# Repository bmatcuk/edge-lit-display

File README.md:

# Edge-lit Display
This repository contains everything you need to build an edge-lit display using
RGB LEDs and laser etched acrylic with a laser cut enclosure.

## System Overview
The display is controlled by an [ATmega32U4], the same microcontroller used in
several [Arduino] boards. It is flashed as an [Arduino Leonardo] over the ICSP
header to make it easier to work with, using an actual [Arduino] as the
programmer. The design surrounding the [ATmega32U4] support circuitry, including
the USB connections, is based on the [Arduino Leonardo] schematics.

The microcontroller communicates with a [TLC5971] over SPI to drive the eight
RGB LEDs. The [TLC5971] is a 12-channel, constant-current sink, 16-bit PWM LED
driver (ie, capable of driving four RGB LEDs at a time). Therefore, the eight
RGB LEDs are divided into two groups and time-multiplexed by the
microcontroller using two high-side PMOS transistors. This allows us to address
each channel of each LED individually.

This circuit is then fitted into a laser cut enclosure with the LEDs directed
into the edge of a laser etched acrylic display. The code on the
microcontroller cycles the colors of the LEDs by rotating through all possible
values for "hue" in the HCY (hue-chroma-luma) colorspace, and converting to 16-
bit RGB for transmission to the [TLC5971].

The whole thing is powered using a standard USB 2.0 cable and includes a
potentiometer to control the brightness of the LEDs by varying the current-
setting resistance of the [TLC5971].

## Schematics
Schematics were designed in [KiCad] v4. This repository has a dependency on my
own [part library] and assumes that my [part library] is located in the same
path as this repository (ie, the `edge-lit display` and `bmatcuk-kicad-library`
directories live in the same directory).

This first schematic is the [ATmega32U4], USB, and support circuitry:

The next schematic connects the microcontroller to the LEDs, driver, and high-
side PMOS to time-multiplex the LED groups:

## PCB Layout
The PCB was designed in [KiCad] v4. This repository has a dependency on my
own [part library] and assumes that my [part library] is located in the same
path as this repository (ie, the `edge-lit display` and `bmatcuk-kicad-library`
directories live in the same directory).

The circuit is laid out as a two-layer design. The front layer contains all of
the components and a ground plane with the back layer as a signal layer. This
is probably the weakest part of the whole project as this is the first time
I've laid out a circuit with so many surface mount components in a constrained
space.

## Enclosure
The enclosure was designed in [FreeCAD] 0.17 assuming it would be made out of
MDF wood with a thickness of 0.251in and laser kerf of 0.011in. The screen
was designed for acrylic with a thickness of 3mm and a laser kerf of 0.2mm.
These values can be easily modified in [FreeCAD] by editing the spreadsheet
called "Datum"; the rest of the design will update automatically.

Once the design was complete, 2D projections were made of each piece and these
projections were exported as "flattened svgs". The resulting svg was edited in
[Inkscape] to conform to the format that the manufacturer wanted (ie, to make
the cuts blue, for example).

The svg below might be really difficult to see on your screen because the
stroke width is only 0.01mm. This was a requirement from where I had the
parts laser cut.

## Acrylic Screen
The outline of the screen was designed in [FreeCAD] with the enclosure. Once
the 2D projection was exported as an svg (as mentioned above), it was imported
into [Inkscape] to create the design. Originally, I was going to do some sort
of cityscape, but then I thought it would be more fun to tie this back to a
previous passion project of mine: [lasercat.party] (github: [lasercatparty])!

I edited the photo of the cat in [Photoshop] to remove the background, convert
to greyscale, and then darken some of the light areas with the burn tool, and
lighten some of the dark areas with the dodge tool. The image was then imported
into [Inkscape] and I used the "Trace Bitmap" function to vectorize it. This
was an iterative process: adjusting light and dark areas in [Photoshop], re-
importing in [Inkscape] to vectorize, etc, until I was happy with the result.
The rest of the design was done entirely in [Inkscape]. Then everything was
grouped together and flipped horizontally so that it could be etched on the
back of the acrylic.

The [Photoshop] file is also included in this repository (cat.psd).

Like above, it may be difficult to make out the edge cuts on your screen
because the stroke width is 0.01mm.

## Manufacturing
The first step was getting the PCB, enclosure, and screen manufactured. I sent
the gerbers to [ALLPCB.com] for PCB manufacturing. I'm very impressed with them
and would definitely recommend. I had the boards in my hands in less than a week
and their prices are very reasonable! The enclosure and screen svgs were sent to
[Ponoko] for laser cutting and etching. Therefore, the MDF and acrylic
thicknesses and kerfs match their specs, and the files are formatted to their
liking (blue for cuts, black for area engraving, red for line engraving; stroke
width of 0.01mm). All electrical components were ordered from [DigiKey]. This
repository includes a Bill Of Material file called `edge-lit display.csv` which
includes all of the [DigiKey] part numbers. You can upload the file to their
website to add all of the parts to your cart.

## Build Log
### Soldering
With PCB and components in hand, the next step is soldering the PCB. We want to
load the [Arduino] bootloader onto our [ATmega32U4], so the first thing we'll
solder is the microcontroller and support circuitry. Installing the [Arduino]
bootloader is done via the ICSP header which uses the SPI pins on the
microcontroller; these pins are also used to control the [TLC5971], so we're
going to leave that and most of the circuitry around it off our board for now.

*Technically*, I think it would be ok to solder everything before installing
the bootloader because it's unlikely that any of the data will make sense to
the [TLC5971] and the microcontroller will tri-state all of the IO pins while
flashing so all of the LEDs will be off anyway, but why risk it? Besides,
pausing to flash the microcontroller mid-solder gives us an opportunity to
make sure everything is working up to that point; troubleshooting will be
easier with fewer components on the board.

That said, I soldered all of the passives (resistors, capacitors, and the
ferrite beads), the varistors, fuse, ICSP header, diode, and [ATmega32U4]. I
technically didn't need to solder all of the passive components, since some of
them are support circuitry for the [TLC5971], but it was easier to solder them
all together. I then tested for any bridged pins with a multimeter, and, when I
was satisfied everything looked good, I moved on to installing the bootloader.

Some tips for soldering: I did most of the soldering with a soldering iron
(my trusty [Hakko FX-888D]) with a beveled tip (the [T18-CF15]). It's possible
to solder everything this way with the liberal application of flux (I have a
[Kester 186 Flux Pen]) - search for "drag soldering" tutorials. I found it
was easier to solder first using this method, and then touch things up a bit
with a hot air rework station (I'm using an [Aoyue Int866]). For example, I
soldered the [ATmega32U4] a little off-center; very hard to fix with an iron,
but short work for the hot air station.

### The Bootloader
To install the bootloader, I flashed an [Arduino Uno] with the ArduinoISP. To
do this in the [Arduino] IDE, select the Uno as the device and open the
ArduinoISP example sketch. Make sure all of the `#define`s are right at the
top of the file and then upload the sketch to the Uno. Next, disconnect the
Uno from your computer and make the following connections:
* 5V on the Uno to pin 2 of the ICSP
* GND on the Uno to pin 6 on the ICSP
* D10 on the Uno (reset signal) to pin 5 on the ICSP
* D11 on the Uno (MOSI) to pin 4 on the ICSP
* D12 on the Uno (MISO) to pin 1 on the ICSP
* D13 on the Uno (SCK) to pin 3 on the ICSP

Other [Arduino]s can be used in place of the [Arduino Uno] using a similar
process. You just need to figure out what pins are used for SPI (MOSI, MISO,
and SCK) and the reset pin. You can actually change the pins in the `#define`s
at the top of the ArduinoISP sketch.

Anyway, once the wired connections are made, reconnect the [Arduino Uno] to
your computer. Select the [Arduino Leonardo] from the device menu, set the port
to where the Uno is connected, change "programmer" to "Arduino as ISP", and
select "Burn Bootloader". This process will take a couple minutes, but it will
test to make sure installation was successful, so if you don't see any errors,
you know your soldering, at least up to this point, is good.

### Soldering Part Deux
After the bootloader is installed, disconnect the [Arduino Uno] and solder
the rest of the components. Now the sketch can be flashed via USB! Connect the
PCB to your computer via USB. If all your soldering went well, you should be
able to flash the code to it by selecting the [Arduino Leonardo] device from the
[Arduino] IDE and uploading. You should hopefully see the LEDs cycle through
all of the colors of the rainbow!

### Constructing the Enclosure
Putting the case together is fairly straightforward, but you may find that the
slots are fairly tight. The company I ordered my lasercut parts from ([Ponoko])
didn't have very accurate measurements for wood thickness or kerf. I found the
wood they sent me was around 1.5mm thicker then I was expecting. I had to use a
wood file to make the pieces fit together, and, even then, they were so snug I
didn't bother using any glue.

Basically, you want to put the bottom and sides together, gluing if necessary.
I put the lasercut side (with the burn marks) on the inside to hide it. Then
fit the PCB in. I had planned on using some M2 nylon stand-offs to mount the
PCB (hence the little holes in the top and bottom pieces), but the holes ended
up being too small to thread the stand-offs through. So, instead, I just
hammered some nails through the bottom to keep the PCB from sliding around.

Next, slide the acrylic display through the top piece and put the top of the
enclosure on. The slots on the side pieces should keep the acrylic from falling
over, and should line it up to be right on top of the LEDs. If you are
sucessfully using stand-offs, you can have some stand-offs go to the top of the
enclosure, too.

I adjusted some of the calculations in the [FreeCAD] model after I received my
lasercut enclosure to hopefully make it less snug. I also regenerated the
enclosure.svg file, but I haven't tried getting another enclosure made up.

## License
Software in this repository is licensed under the [MIT] license. Hardware
schematics are released under a Creative Commons Attribution and Share Alike
license ([CC-BY-SA] 4.0). PCB layout designs, enclosure designs, and acrylic
display designs are licensed under a Creative Commons Attribution, Non-
Commercial, Share Alike license ([CC-BY-NC-SA] 4.0).

[ALLPCB.com]: http://www.allpcb.com/
[ATmega32U4]: http://www.microchip.com/wwwproducts/en/ATmega32u4
[Aoyue Int866]: https://www.aoyue.eu/aoyue-int866-3in1-rework-station-lead-free-hot-air-soldering-station.html
[Arduino Leonardo]: https://store.arduino.cc/usa/arduino-leonardo-with-headers
[Arduino Uno]: https://store.arduino.cc/usa/arduino-uno-rev3
[Arduino]: https://www.arduino.cc/
[CC-BY-NC-SA]: https://creativecommons.org/licenses/by-nc-sa/4.0/
[CC-BY-SA]: https://creativecommons.org/licenses/by-sa/4.0/
[DigiKey]: https://www.digikey.com/
[FreeCAD]: https://www.freecadweb.org/
[Hakko FX-888D]: https://www.hakkousa.com/products/soldering/hakko-fx-888d-digital-soldering-station-10145.html
[Inkscape]: https://inkscape.org/
[Kester 186 Flux Pen]: https://www.kester.com/products/product/186-flux-pen
[KiCad]: http://kicad-pcb.org/
[MIT]: https://choosealicense.com/licenses/mit/
[Photoshop]: https://www.adobe.com/products/photoshop.html
[Ponoko]: https://www.ponoko.com/
[T18-CF15]: https://www.hakkousa.com/products/soldering-iron-tips/t18-series/t18-cf15.html
[TLC5971]: http://www.ti.com/product/TLC5971
[lasercat.party]: http://lasercat.party
[lasercatparty]: https://github.com/bmatcuk/lasercatparty
[part library]: https://github.com/bmatcuk/bmatcuk-kicad-library/

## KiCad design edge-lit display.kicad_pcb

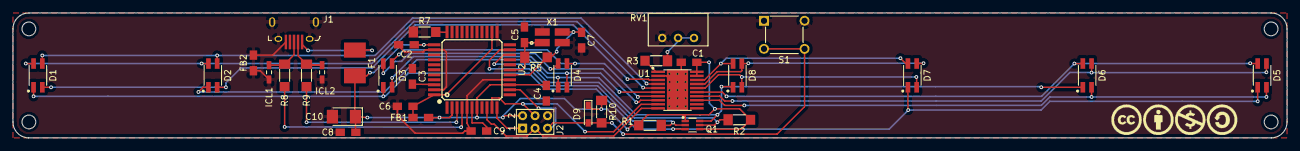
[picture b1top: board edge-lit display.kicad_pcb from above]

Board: 2 copper layers, 204.0 x 20.0 mm, 40 parts (0 on the bottom side), 35 nets.

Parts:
C1, C2, C3, C4, C8: 100nF; 0805
C5, C7: 12pF; 0805
C6, C9: 1uF; 0805
C10: 10uF; 1210
D1, D2, D3, D4, D5, D6, D7, D8: LED_ARGB; PLCC4
D9: 1N4148WS; SOD-323FL
F1: Fuse-500mA; 1812_Concave
FB1, FB2: Ferrite_Bead_30Ohm; 0805
ICL1, ICL2: Varistor; 0603
J1: USB-Micro-B; USB_Micro_B_Female
J2: CONN_03X2FEMALE; 2X3
Q1: Dual-PMOS; SOT-363
R1, R2, R7, R10: 10k; 1206
R3: 3.3k; 1206
R5: 1M; 1206
R8, R9: 22; 1206
RV1: 10k; Bourns_3310C
S1: SPST-NO; SPST_6mm
U1: TLC59711PWPR; HTSSOP-20
U2: ATMEGA32U4TQFP-44; TQFP44
X1: 16MHZ; 4SMD

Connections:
+5V: C1.1, C2.1, C4.1, C8.1, C10.1, D9.1, F1.1, FB1.1, J2.2, Q1.1, Q1.4, R1.1, R2.1, R10.2, U1.19, U1.20, U2.2, U2.7, U2.14, U2.34
/Arduino Compatible/AREF: C3.1, U2.42
/Arduino Compatible/AVCC: C6.1, FB1.2, U2.24, U2.44
/Arduino Compatible/D0: Q1.5, R2.2, U2.20
/Arduino Compatible/D1: Q1.2, R1.2, U2.21
/Arduino Compatible/D14/MISO: J2.1, U2.11
/Arduino Compatible/D15/SCK: J2.3, U1.10, U2.9
/Arduino Compatible/D16/MOSI: J2.4, U1.9, U2.10
/Arduino Compatible/D+: R8.1, U2.4
/Arduino Compatible/D-: R9.1, U2.3
/Arduino Compatible/RESET: D9.2, J2.5, R10.1, S1.3, S1.4, U2.13
/Arduino Compatible/XTAL1: C5.1, R5.2, U2.17, X1.1
/Arduino Compatible/XTAL2: C7.1, R5.1, U2.16, X1.3
GNDA: C1.2, C2.2, C3.2, C4.2, C5.2, C6.2, C7.2, C8.2, C9.2, C10.2, FB2.1, FB2.2, ICL1.2, ICL2.2, J1.5, J1.6, J2.6, R7.2, RV1.3, S1.1, S1.2, U1.2, U1.21, U2.5, U2.15, U2.23, U2.35, U2.43, X1.2, X1.4
unnamed: C9.1, U2.6
unnamed: D1.1, D3.1, D5.1, D7.1, Q1.3
unnamed: D1.2, D2.2, U1.3
unnamed: D1.3, D2.3, U1.4
unnamed: D1.4, D2.4, U1.5
unnamed: D2.1, D4.1, D6.1, D8.1, Q1.6
unnamed: D3.2, D4.2, U1.6
unnamed: D3.3, D4.3, U1.7
unnamed: D3.4, D4.4, U1.8
unnamed: D5.2, D6.2, U1.13
unnamed: D5.3, D6.3, U1.14
unnamed: D5.4, D6.4, U1.15
unnamed: D7.2, D8.2, U1.16
unnamed: D7.3, D8.3, U1.17
unnamed: D7.4, D8.4, U1.18
unnamed: F1.2, J1.1
unnamed: ICL1.1, J1.3, R8.2
unnamed: ICL2.1, J1.2, R9.2
unnamed: R3.1, U1.1
unnamed: R3.2, RV1.1, RV1.2
unnamed: R7.1, U2.33
